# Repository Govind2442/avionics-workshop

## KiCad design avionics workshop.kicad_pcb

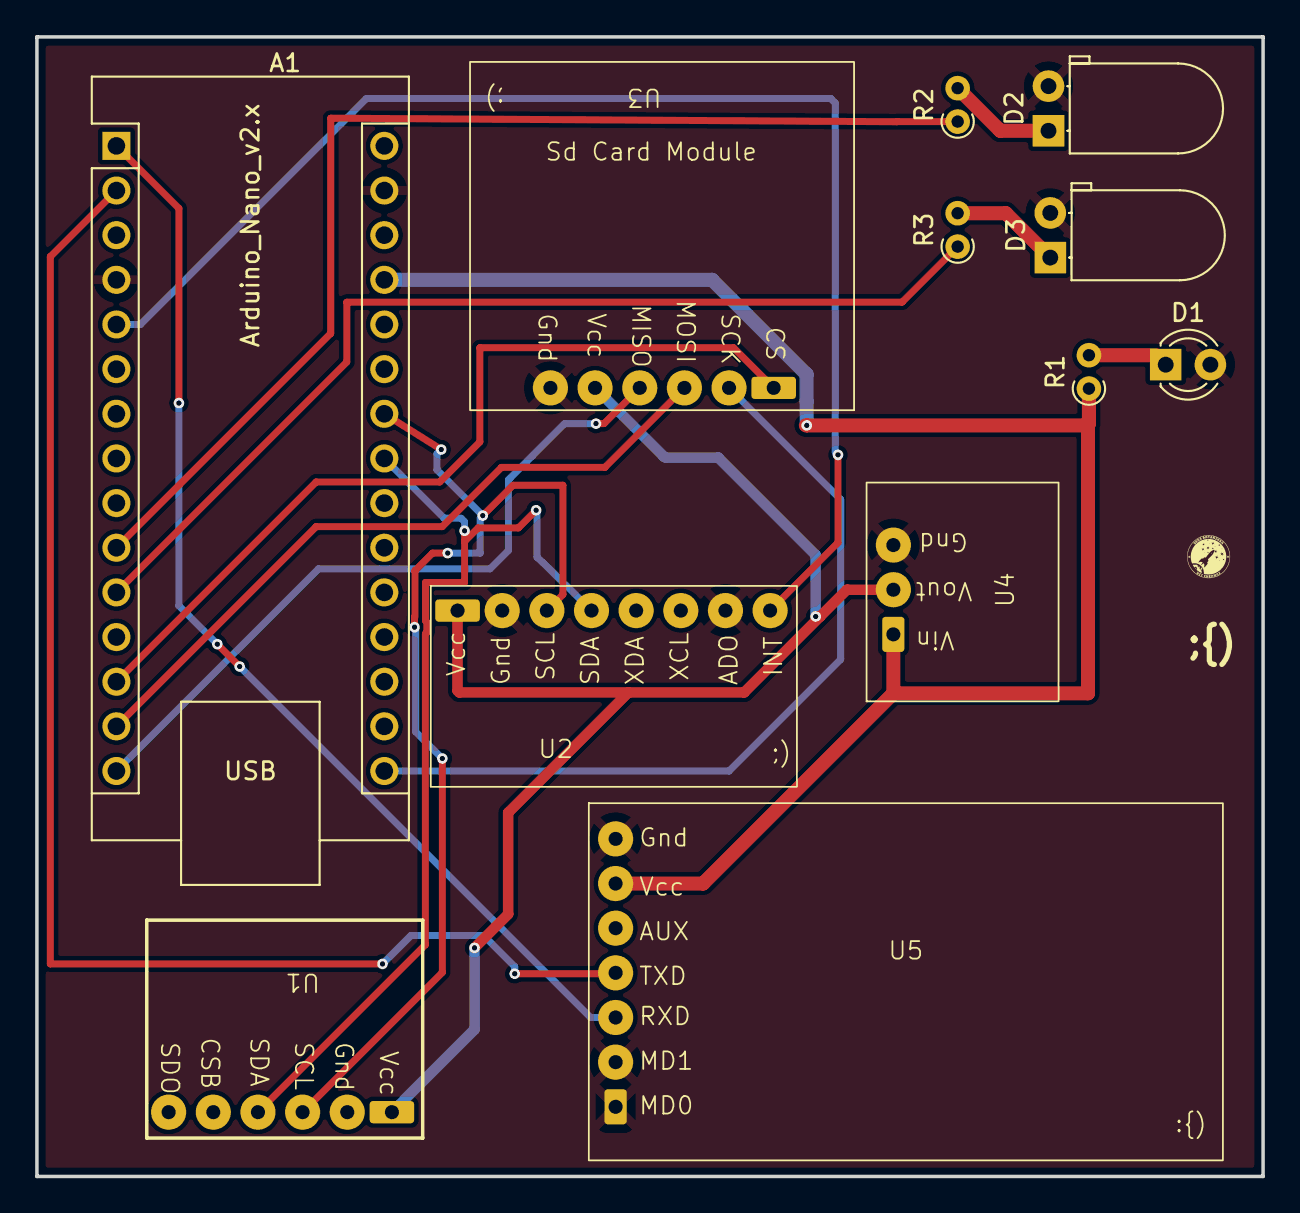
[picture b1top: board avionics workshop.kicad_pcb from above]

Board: 2 copper layers, 69.7 x 64.8 mm, 12 parts (0 on the bottom side), 17 nets.

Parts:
A1: Arduino_Nano_v2.x; Arduino_Nano
D1: LED; LED_D3.0mm
D2: LED; LED_D5.0mm_Horizontal_O1.27mm_Z3.0mm
D3: LED; LED_D5.0mm_Horizontal_O1.27mm_Z3.0mm_Clear
R1, R2, R3: 330; R_Axial_DIN0204_L3.6mm_D1.6mm_P1.90mm_Vertical
U1: BMP280
U2: MPU-6050
U3: Sd card module
U4: AMS1117-3.3; AMS-1117
U5: AS32-TTL100

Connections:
+5V: A1.27 (+5V), R1.1, U4.1 (GND), U5.6 (Vcc)
/D2: A1.5 (D2), U2.8 (INT)
/L2: A1.10 (D7), R2.1
/L3: A1.11 (D8), R3.1
/MISO: A1.15 (D12), U3.4 (MISO)
/MOSI: A1.14 (D11), U3.3 (MOSI)
/PWR(3.3): U1.1 (GND), U2.1, U3.5 (Vcc), U4.2 (VO)
/RXD: A1.1 (D1/TX), U5.3 (RXD)
/SCK: A1.16 (D13), U3.2 (SCK)
/SCL: A1.24 (A5), U1.3 (SDI), U2.3 (SCL)
/SDA: A1.23 (A4), U1.4 (SCK), U2.4 (SDA)
/TXD: A1.2 (D0/RX), U5.4 (TXD)
/cs: A1.13 (D10), U3.1 (CS)
GND: A1.4 (GND), A1.29 (GND), D1.2 (A), D2.2 (A), D3.2 (A), U2.2 (Gnd), U2.7 (ADO), U3.6 (Gnd), U4.3 (VI), U5.1 (MD0), U5.2 (MD1), U5.7 (Gnd)
unnamed: D1.1 (K), R1.2
unnamed: D2.1 (K), R2.2
unnamed: D3.1 (K), R3.2

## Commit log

2025-08-25 draft1
2025-08-27 draft2
2025-08-30 draft3
2025-08-31 draft4
2025-08-31 draft7
